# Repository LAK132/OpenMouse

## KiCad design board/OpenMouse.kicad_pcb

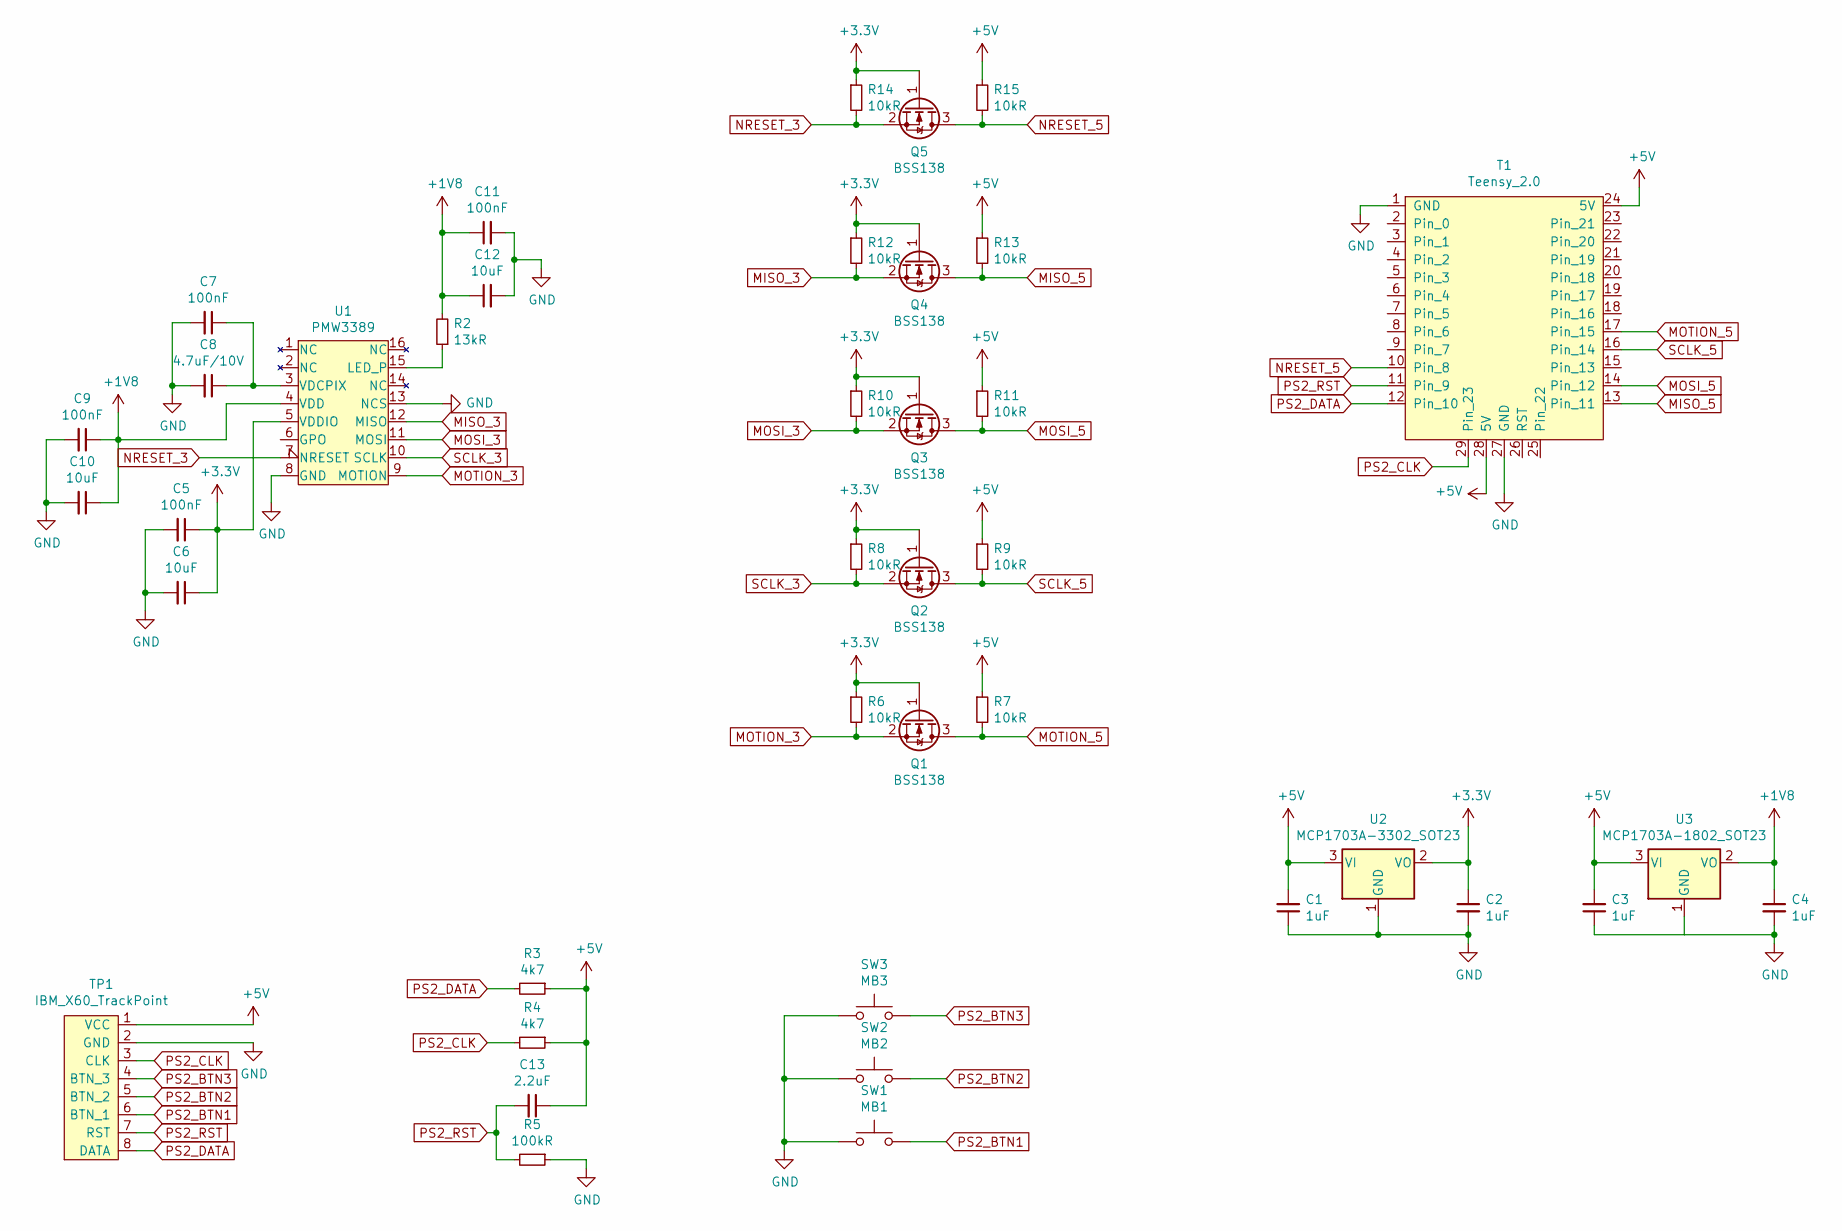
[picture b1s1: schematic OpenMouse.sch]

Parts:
C1, C2, C3, C4: 1uF; C_0805_2012Metric_Pad1.15x1.40mm_HandSolder
C5, C7, C9, C11: 100nF; C_0805_2012Metric_Pad1.15x1.40mm_HandSolder
C6, C10, C12: 10uF; C_0805_2012Metric_Pad1.15x1.40mm_HandSolder
C8: 4.7uF/10V; C_0805_2012Metric_Pad1.15x1.40mm_HandSolder
C13: 2.2uF; C_0805_2012Metric_Pad1.15x1.40mm_HandSolder
Q1, Q2, Q3, Q4, Q5: BSS138; SOT-23
R2: 13kR; R_0805_2012Metric_Pad1.15x1.40mm_HandSolder
R3, R4: 4k7; R_0805_2012Metric_Pad1.15x1.40mm_HandSolder
R5: 100kR; R_0805_2012Metric_Pad1.15x1.40mm_HandSolder
R6, R7, R8, R9, R10, R11, R12, R13, R14, R15: 10kR; R_0805_2012Metric_Pad1.15x1.40mm_HandSolder
SW1: MB1; PinHeader_1x02_P2.54mm_Vertical
SW2: MB2; PinHeader_1x02_P2.54mm_Vertical
SW3: MB3; PinHeader_1x02_P2.54mm_Vertical
T1: Teensy_2.0
TP1: IBM_X60_TrackPoint; PinHeader_1x08_P2.54mm_Vertical
U1: PMW3389
U2: MCP1703A-3302_SOT23; SOT-23
U3: MCP1703A-1802_SOT23; SOT-23

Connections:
+1V8: C4.1, C9.1, C10.1, C11.1, C12.1, R2.2, U1.4 (VDD), U3.2 (VO)
+3V3: C2.1, C5.1, C6.1, Q1.1 (G), Q2.1 (G), Q3.1 (G), Q4.1 (G), Q5.1 (G), R6.1, R8.1, R10.1, R12.1, R14.1, U1.5 (VDDIO), U2.2 (VO)
+5V: C1.2, C3.2, C13.1, R3.1, R4.1, R7.1, R9.1, R11.1, R13.1, R15.1, T1.24 (5V), T1.28 (5V), TP1.1 (VCC), U2.3 (VI), U3.3 (VI)
GND: C1.1, C2.2, C3.1, C4.2, C5.2, C6.2, C7.2, C8.2, C9.2, C10.2, C11.2, C12.2, R5.1, SW1.1, SW2.1, SW3.1, T1.1 (GND), T1.27 (GND), TP1.2 (GND), U1.8 (GND), U1.13 (NCS), U2.1 (GND), U3.1 (GND)
MISO_3: Q4.2 (S), R12.2, U1.12 (MISO)
MISO_5: Q4.3 (D), R13.2, T1.13 (Pin_11)
MOSI_3: Q3.2 (S), R10.2, U1.11 (MOSI)
MOSI_5: Q3.3 (D), R11.2, T1.14 (Pin_12)
MOTION_3: Q1.2 (S), R6.2, U1.9 (MOTION)
MOTION_5: Q1.3 (D), R7.2, T1.17 (Pin_15)
NRESET_3: Q5.2 (S), R14.2, U1.7 (NRESET)
NRESET_5: Q5.3 (D), R15.2, T1.10 (Pin_8)
unnamed: C7.1, C8.1, U1.3 (VDCPIX)
unnamed: R2.1, U1.15 (LED_P)
PS2_BTN1: SW1.2, TP1.6 (BTN_1)
PS2_BTN2: SW2.2, TP1.5 (BTN_2)
PS2_BTN3: SW3.2, TP1.4 (BTN_3)
PS2_CLK: R4.2, T1.29 (Pin_23), TP1.3 (CLK)
PS2_DATA: R3.2, T1.12 (Pin_10), TP1.8 (DATA)
PS2_RST: C13.2, R5.2, T1.11 (Pin_9), TP1.7 (RST)
SCLK_3: Q2.2 (S), R8.2, U1.10 (SCLK)
SCLK_5: Q2.3 (D), R9.2, T1.16 (Pin_14)

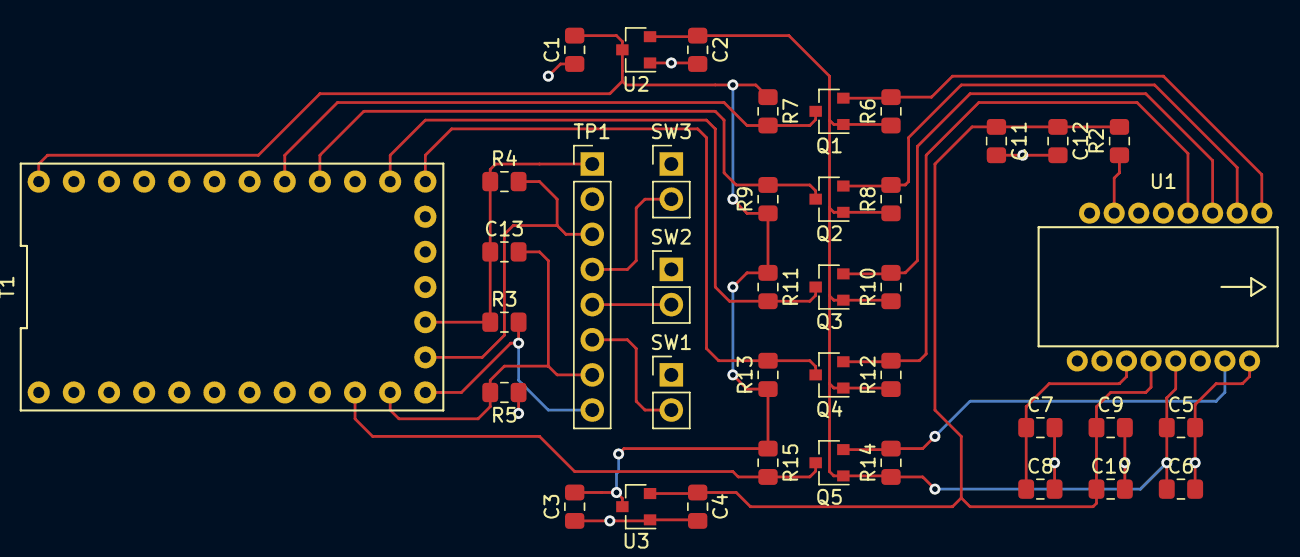
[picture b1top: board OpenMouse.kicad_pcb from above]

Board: 2 copper layers, 40 parts (0 on the bottom side), 22 nets.

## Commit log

2019-01-02 Add gitignore
2019-01-02 Initial design
2019-01-02 Add schematic PDF
2019-02-05 Reroute 5V line to reduce vias
